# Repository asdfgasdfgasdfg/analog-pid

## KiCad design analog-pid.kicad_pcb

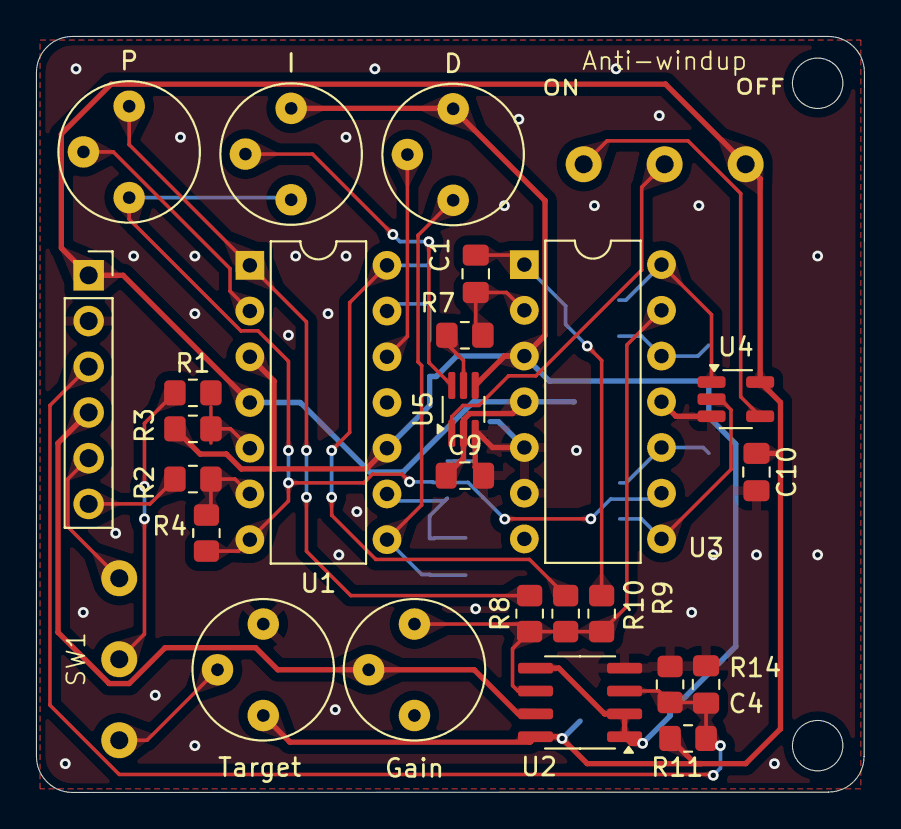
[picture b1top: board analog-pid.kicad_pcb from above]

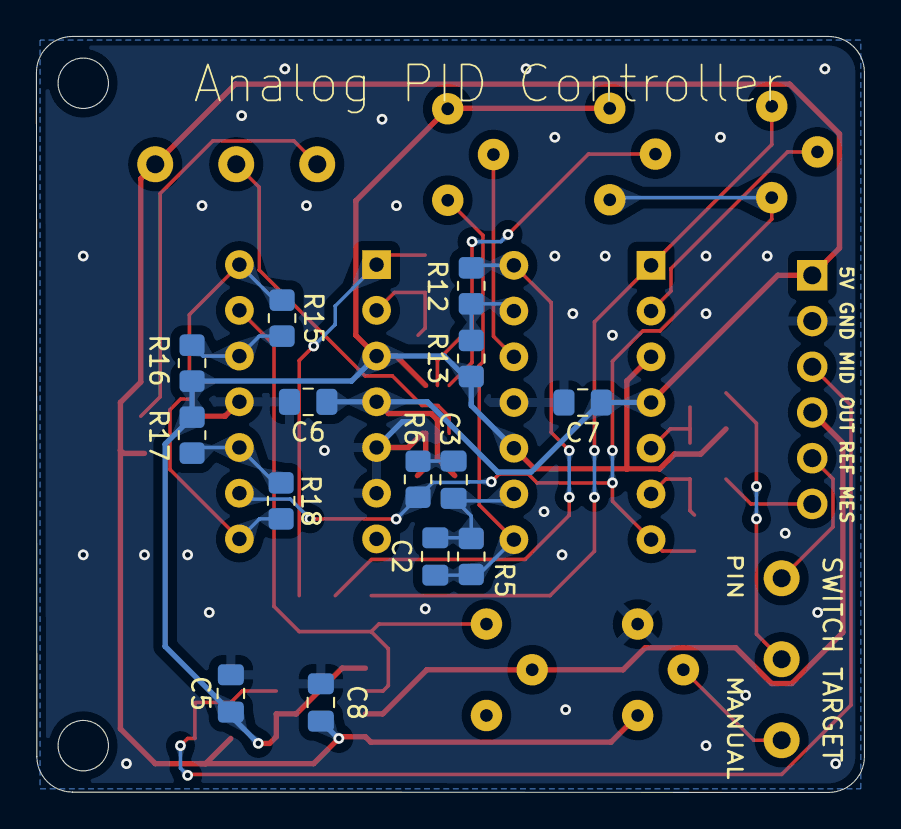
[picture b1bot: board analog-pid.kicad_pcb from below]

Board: 2 copper layers, 46.0 x 42.0 mm, 41 parts (14 on the bottom side), 31 nets.

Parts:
Anti-windup: SS12D10; SS12D10 SPDT Switch
C1, C4, C5, C6, C7, C8, C9, C10: 100nF; C_0805_2012Metric_Pad1.18x1.45mm_HandSolder
C2: 100pF; C_0805_2012Metric_Pad1.18x1.45mm_HandSolder
C3: 1.5nF; C_0805_2012Metric_Pad1.18x1.45mm_HandSolder
D: 10k; Potentiometer_Bourns_3339P_Vertical_HandSoldering
Gain: 10k; Potentiometer_Bourns_3339P_Vertical_HandSoldering
I: 10k; Potentiometer_Bourns_3339P_Vertical_HandSoldering
J1: Conn_01x06_Socket; PinSocket_1x06_P2.54mm_Vertical
P: 10k; Potentiometer_Bourns_3339P_Vertical_HandSoldering
R1, R2, R3, R4, R11, R12, R14: 100k; R_0805_2012Metric_Pad1.20x1.40mm_HandSolder
R5, R7: 1Meg; R_0805_2012Metric_Pad1.20x1.40mm_HandSolder
R6, R13, R16, R17: 10k; R_0805_2012Metric_Pad1.20x1.40mm_HandSolder
R8, R9, R10: 5k; R_0805_2012Metric_Pad1.20x1.40mm_HandSolder
R15, R18: 1k; R_0805_2012Metric_Pad1.20x1.40mm_HandSolder
SW1: SS12D10; SS12D10 SPDT Switch
Target: 10k; Potentiometer_Bourns_3339P_Vertical_HandSoldering
U1, U3: MCP6004; DIP-14_W7.62mm
U2: TSV792IDT; SOIC-8_3.9x4.9mm_P1.27mm
U4: NC7SZ86M5X; SOT-23-5_HandSoldering
U5: TS5A4624; SOT-363_SC-70-6_Handsoldering

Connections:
+5V: Anti-windup.3 (A), C6.1, C7.1, C8.1, C9.1, C10.1, J1.1, R11.2, Target.1, U1.4 (V+), U2.8 (V+), U3.4 (V+), U4.5 (VCC), U5.2 (V+)
/D: R10.1, R12.1, U1.14
/Diff: I.1, P.1, R4.2, R6.1, U1.7, U3.9 (-)
/I: C1.2, R9.1, U3.1
/Integrator_Off: Anti-windup.2 (B), U5.1 (IN)
/Measured: J1.6, R2.1
/P: P.3, R8.2, U1.1
/Target_opt: J1.5, SW1.3 (A)
/V-: Gain.3, R8.1, R9.2, R10.2, U2.6 (-), U3.13 (-)
/Vmid: C5.1, D.3, I.3, R3.1, R13.2, R16.1, R17.1, U1.3 (+), U1.10 (+), U2.1, U2.2 (-), U2.5 (+), U3.3 (+), U5.4 (NC)
/Vmid_opt: C4.1, J1.3, R11.1, R14.2, U2.3 (+)
/Vout: Gain.2, J1.4, U2.7
GND: C4.2, C5.2, C6.2, C7.2, C8.2, C9.2, C10.2, J1.2, R14.1, Target.3, U1.11 (V-), U2.4 (V-), U3.5 (+), U3.6 (-), U3.11 (V-), U4.3 (GND), U5.3 (V-)
unnamed: C2.2, D.1, R5.2, U1.8
unnamed: C3.1, R6.2
unnamed: R15.2, U3.14, U4.1
unnamed: R18.2, U3.8, U4.2
unnamed: R1.1, SW1.2 (B)
unnamed: SW1.1 (C), Target.2
unnamed: Anti-windup.1 (C), U4.4
unnamed: P.2, U1.2 (-)
unnamed: R1.2, R3.2, U1.5 (+)
unnamed: R2.2, R4.1, U1.6 (-)
unnamed: C2.1, C3.2, R5.1, U1.9 (-)
unnamed: D.2, U1.12 (+)
unnamed: R12.2, R13.1, U1.13 (-)
unnamed: C1.1, R7.2, U3.2 (-)
unnamed: R17.2, R18.1, U3.10 (+)
unnamed: R15.1, R16.2, U3.12 (+)
unnamed: R7.1, U5.5 (COM)
unnamed: I.2, U5.6 (NO)

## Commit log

2025-04-01 second commit before i add even more fking stuff
2025-04-01 anti windup and decoupling caps added
2025-04-01 Most footprints added
2025-04-01 schematic + footprints done
2025-04-01 Components placed and half the traces
2025-04-01 Added edge cut & fixed silkscreens
2025-04-01 Finished
    Just need to double check, send to fab and order components.
    Also need to test lower frequency differentiator circuit
2025-04-01 Added pin designators. **Need to add testpads too
2025-04-02 Finished
    Test points not needed.
    Gonna skip the TVS diodes.
    Finished decoupling caps.
    Added rounded corners & mounting holes.
2025-04-10 finished
